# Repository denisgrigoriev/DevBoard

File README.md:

# Devboard project

in this project i would be using kicad to create the schematics and pcb layout
and JLCPCB to manufacture the actual pcb.

Parts used:

### Bill of Materials (BOM)

| Part Number | Type | LCSC Part # | Qty | Source | Ext. Price |
| :--- | :---: | :---: | :---: | :---: | :---: |
| **CL05A105KA5NQNC** | Basic | C52923 | 4 | JLCPCB | $0.0612 |
| **MCP1700T-3302E/TT** | Extended | C39051 | 5 | JLCPCB | $2.1540 |
| **0402CG330J500NT** | Basic | C1562 | 4 | JLCPCB | $0.0232 |
| **0402WGF1001TCE** | Basic | C11702 | 4 | JLCPCB | $0.0164 |
| **0402WGF5101TCE** | Basic | C25905 | 4 | JLCPCB | $0.0048 |
| **X322512MSB4SI** | Basic | C9002 | 2 | JLCPCB | $0.1988 |
| **CL10A106KP8NNNC** | Basic | C19702 | 4 | JLCPCB | $0.2208 |
| **0402WGJ0270TCE** | Extended | C25156 | 20 | JLCPCB | $0.0160 |
| **RP2040** | Extended | C2040 | 2 | JLCPCB | $1.9584 |
| **CL05B104KO5NNNC** | Basic | C1525 | 22 | JLCPCB | $0.1364 |
| **W25Q16JVUXIQ** | Extended | C2843335 | 2 | JLCPCB | $3.1444 |
| **0402WGF1002TCE** | Basic | C25744 | 2 | JLCPCB | $0.0070 |
| **TYPE-C-31-M-12** | Extended | C165948 | 2 | JLCPCB | $0.3662 |
| **TS-1088-AR02016** | Basic | C72047 | 2 | JLCPCB | $0.1098 |

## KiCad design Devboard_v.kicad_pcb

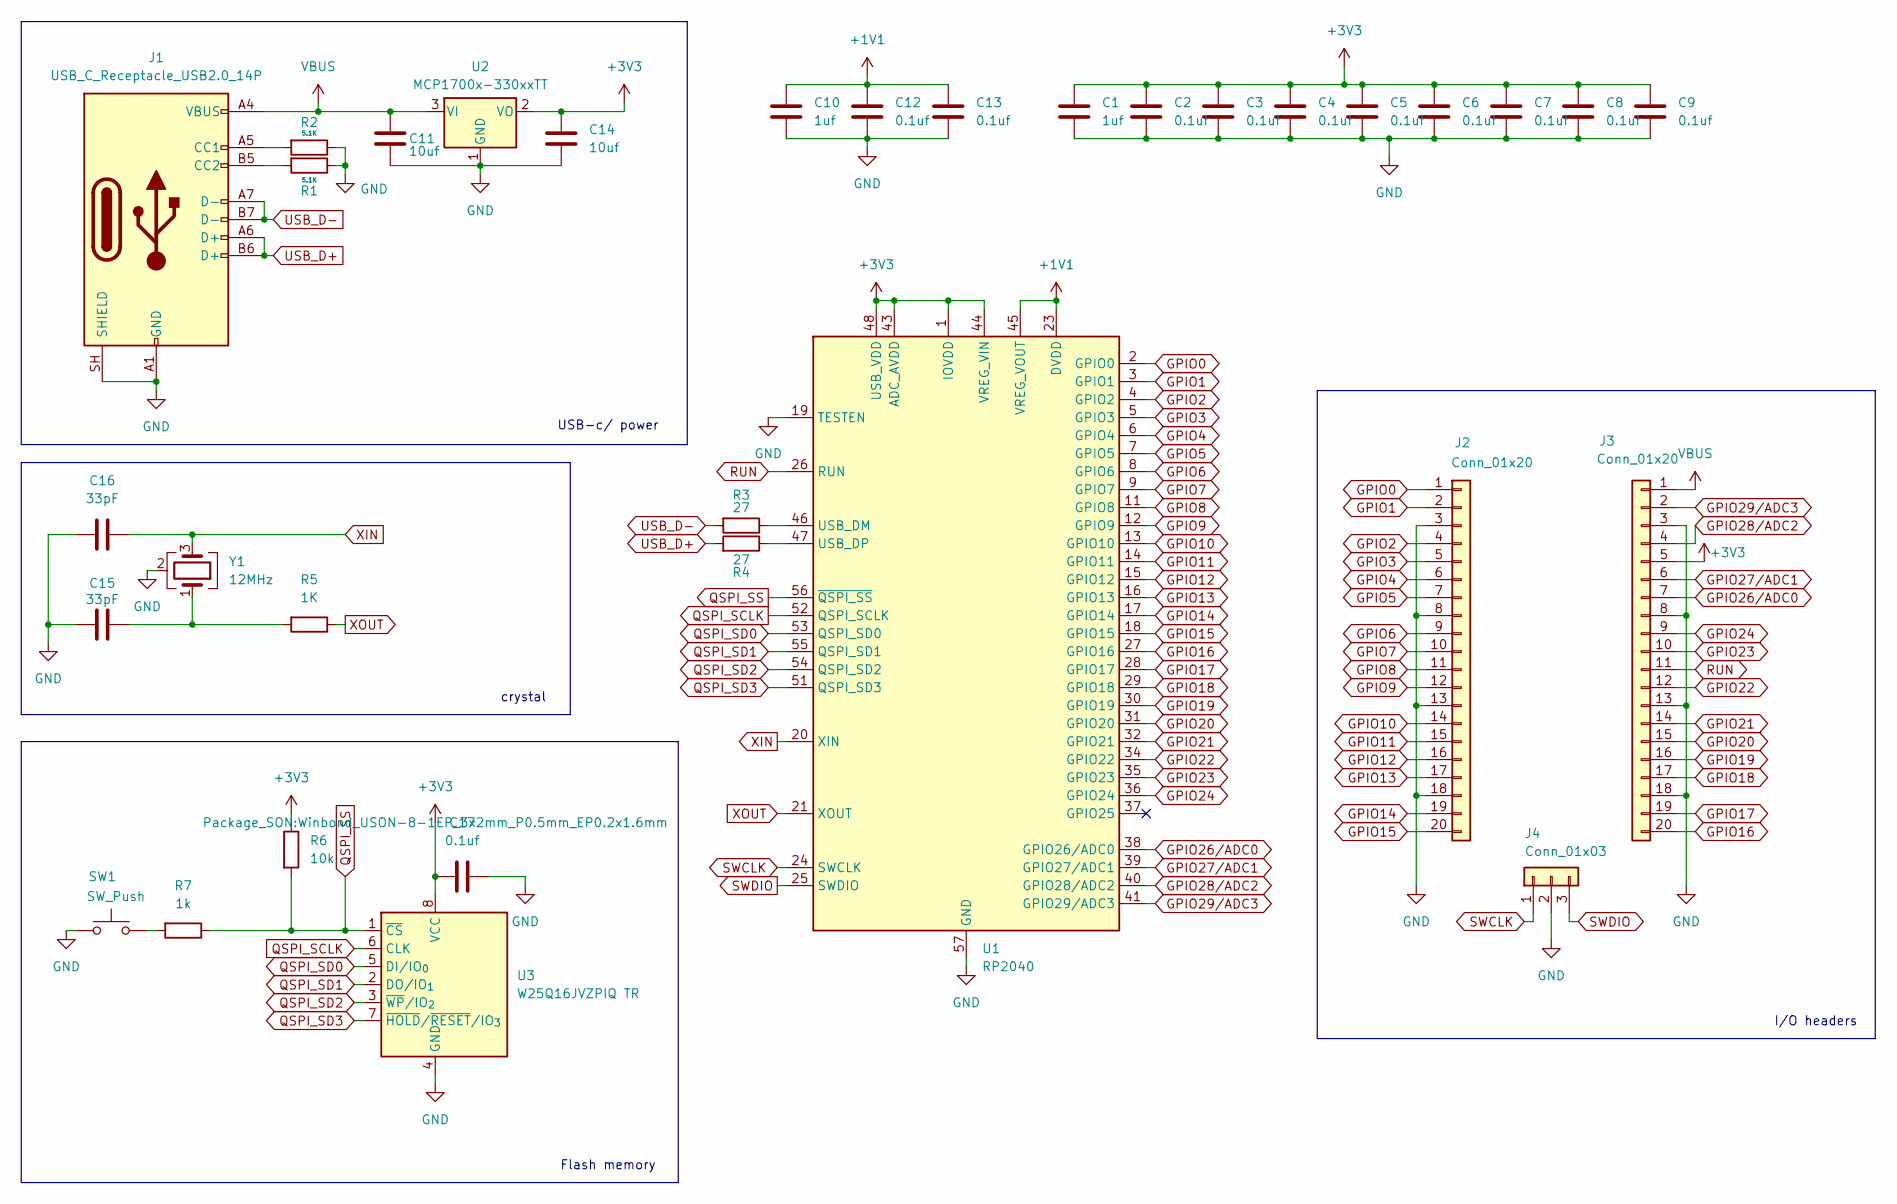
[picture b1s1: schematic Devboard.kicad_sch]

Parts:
C1, C10: 1uf; C_0402_1005Metric
C2, C3, C4, C5, C6, C7, C8, C9, C12, C13, C17: 0.1uf; C_0402_1005Metric
C11, C14: 10uf; C_0603_1608Metric
C15, C16: 33pF; C_0402_1005Metric
J1: USB_C_Receptacle_USB2.0_14P; USB_C_Receptacle_HRO_TYPE-C-31-M-12
J2, J3: Conn_01x20; PinHeader_1x20_P2.54mm_Vertical
J4: Conn_01x03; PinHeader_1x03_P2.54mm_Vertical
R1, R2: 5.1K; R_0402_1005Metric
R3, R4: 27; R_0402_1005Metric
R5: 1K; R_0402_1005Metric
R6: 10k; R_0402_1005Metric
R7: 1k; R_0402_1005Metric
SW1: SW_Push; SW_Push_SPST_NO_Alps_SKRK
U1: RP2040; QFN-56-1EP_7x7mm_P0.4mm_EP3.2x3.2mm
U2: MCP1700x-330xxTT; SOT-23
U3: W25Q16JVZPIQ TR; Winbond_USON-8-1EP_3x2mm_P0.5mm_EP0.2x1.6mm
Y1: 12MHz; Crystal_SMD_3225-4Pin_3.2x2.5mm

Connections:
+1V1: C10.1, C12.1, C13.1, U1.23 (DVDD), U1.45 (VREG_VOUT), U1.50 (DVDD)
+3V3: C1.1, C2.1, C3.1, C4.1, C5.1, C6.1, C7.1, C8.1, C9.1, C14.1, C17.2, J3.5, R6.1, U1.1 (IOVDD), U1.10 (IOVDD), U1.22 (IOVDD), U1.33 (IOVDD), U1.42 (IOVDD), U1.43 (ADC_AVDD), U1.44 (VREG_VIN), U1.48 (USB_VDD), U1.49 (IOVDD), U2.2 (VO), U3.8 (VCC)
GND: C1.2, C2.2, C3.2, C4.2, C5.2, C6.2, C7.2, C8.2, C9.2, C10.2, C11.2, C12.2, C13.2, C14.2, C15.2, C16.2, C17.1, J1.A1 (GND), J1.A12 (GND), J1.B1 (GND), J1.B12 (GND), J1.SH (SHIELD), J2.3, J2.8, J2.13, J2.18, J3.3, J3.8, J3.13, J3.18, J4.2, R1.1, R2.1, SW1.1, U1.19 (TESTEN), U1.57 (GND), U2.1 (GND), U3.4 (GND), Y1.2 (G), Y1.4 (G)
GPIO0: J2.1, U1.2 (GPIO0)
GPIO1: J2.2, U1.3 (GPIO1)
GPIO2: J2.4, U1.4 (GPIO2)
GPIO3: J2.5, U1.5 (GPIO3)
GPIO4: J2.6, U1.6 (GPIO4)
GPIO5: J2.7, U1.7 (GPIO5)
GPIO6: J2.9, U1.8 (GPIO6)
GPIO7: J2.10, U1.9 (GPIO7)
GPIO8: J2.11, U1.11 (GPIO8)
GPIO9: J2.12, U1.12 (GPIO9)
GPIO10: J2.14, U1.13 (GPIO10)
GPIO11: J2.15, U1.14 (GPIO11)
GPIO12: J2.16, U1.15 (GPIO12)
GPIO13: J2.17, U1.16 (GPIO13)
GPIO14: J2.19, U1.17 (GPIO14)
GPIO15: J2.20, U1.18 (GPIO15)
GPIO16: J3.20, U1.27 (GPIO16)
GPIO17: J3.19, U1.28 (GPIO17)
GPIO18: J3.17, U1.29 (GPIO18)
GPIO19: J3.16, U1.30 (GPIO19)
GPIO20: J3.15, U1.31 (GPIO20)
GPIO21: J3.14, U1.32 (GPIO21)
GPIO22: J3.12, U1.34 (GPIO22)
GPIO23: J3.10, U1.35 (GPIO23)
GPIO24: J3.9, U1.36 (GPIO24)
GPIO26/ADC0: J3.7, U1.38 (GPIO26/ADC0)
GPIO27/ADC1: J3.6, U1.39 (GPIO27/ADC1)
GPIO28/ADC2: J3.4, U1.40 (GPIO28/ADC2)
GPIO29/ADC3: J3.2, U1.41 (GPIO29/ADC3)
unnamed: C15.1, R5.2, Y1.1
unnamed: J1.A5 (CC1), R2.2
unnamed: J1.B5 (CC2), R1.2
unnamed: R7.2, SW1.2
unnamed: R3.1, U1.46 (USB_DM)
unnamed: R4.1, U1.47 (USB_DP)
QSPI_SCLK: U1.52 (QSPI_SCLK), U3.6 (CLK)
QSPI_SD0: U1.53 (QSPI_SD0), U3.5 (DI/IO_{0})
QSPI_SD1: U1.55 (QSPI_SD1), U3.2 (DO/IO_{1})
QSPI_SD2: U1.54 (QSPI_SD2), U3.3 (~WP/IO_{2})
QSPI_SD3: U1.51 (QSPI_SD3), U3.7 (~HOLD/~RESET/IO_{3})
QSPI_SS: R6.2, R7.1, U1.56 (~QSPI_SS), U3.1 (~CS)
RUN: J3.11, U1.26 (RUN)
SWCLK: J4.1, U1.24 (SWCLK)
SWDIO: J4.3, U1.25 (SWDIO)
USB_D+: J1.A6 (D+), J1.B6 (D+), R4.2
USB_D-: J1.A7 (D-), J1.B7 (D-), R3.2
VBUS: C11.1, J1.A4 (VBUS), J1.A9 (VBUS), J1.B4 (VBUS), J1.B9 (VBUS), J3.1, U2.3 (VI)
XIN: C16.1, U1.20 (XIN), Y1.3
XOUT: R5.1, U1.21 (XOUT)

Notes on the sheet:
I/O headers
Flash memory
crystal
USB-c/ power

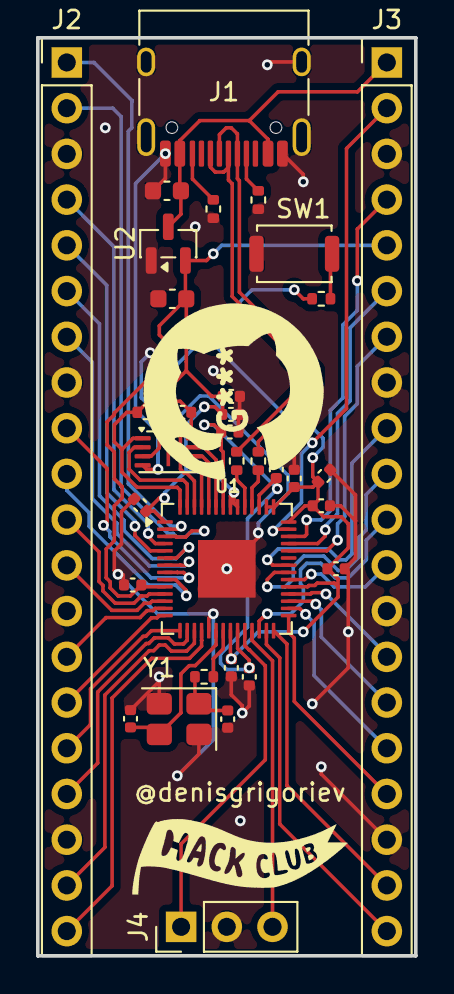
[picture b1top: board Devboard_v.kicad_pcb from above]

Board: 2 copper layers, 21.0 x 51.0 mm, 33 parts (0 on the bottom side), 52 nets.

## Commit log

2026-06-25 PCB files
2026-06-25 Add README for Devboard project with BOM
    This README provides details about the Devboard project, including the tools used for PCB design and manufacturing, along with a Bill of Materials (BOM) listing the parts used.
2026-06-25 Fix heading formatting in README.md
    Added a space after the heading for better formatting.
2026-06-25 Add images to README for project visualization
    Added images to illustrate the project.
2026-06-26 Enhance README with additional images
    Added additional images to the README for better visualization.
2026-06-26 .sch file
